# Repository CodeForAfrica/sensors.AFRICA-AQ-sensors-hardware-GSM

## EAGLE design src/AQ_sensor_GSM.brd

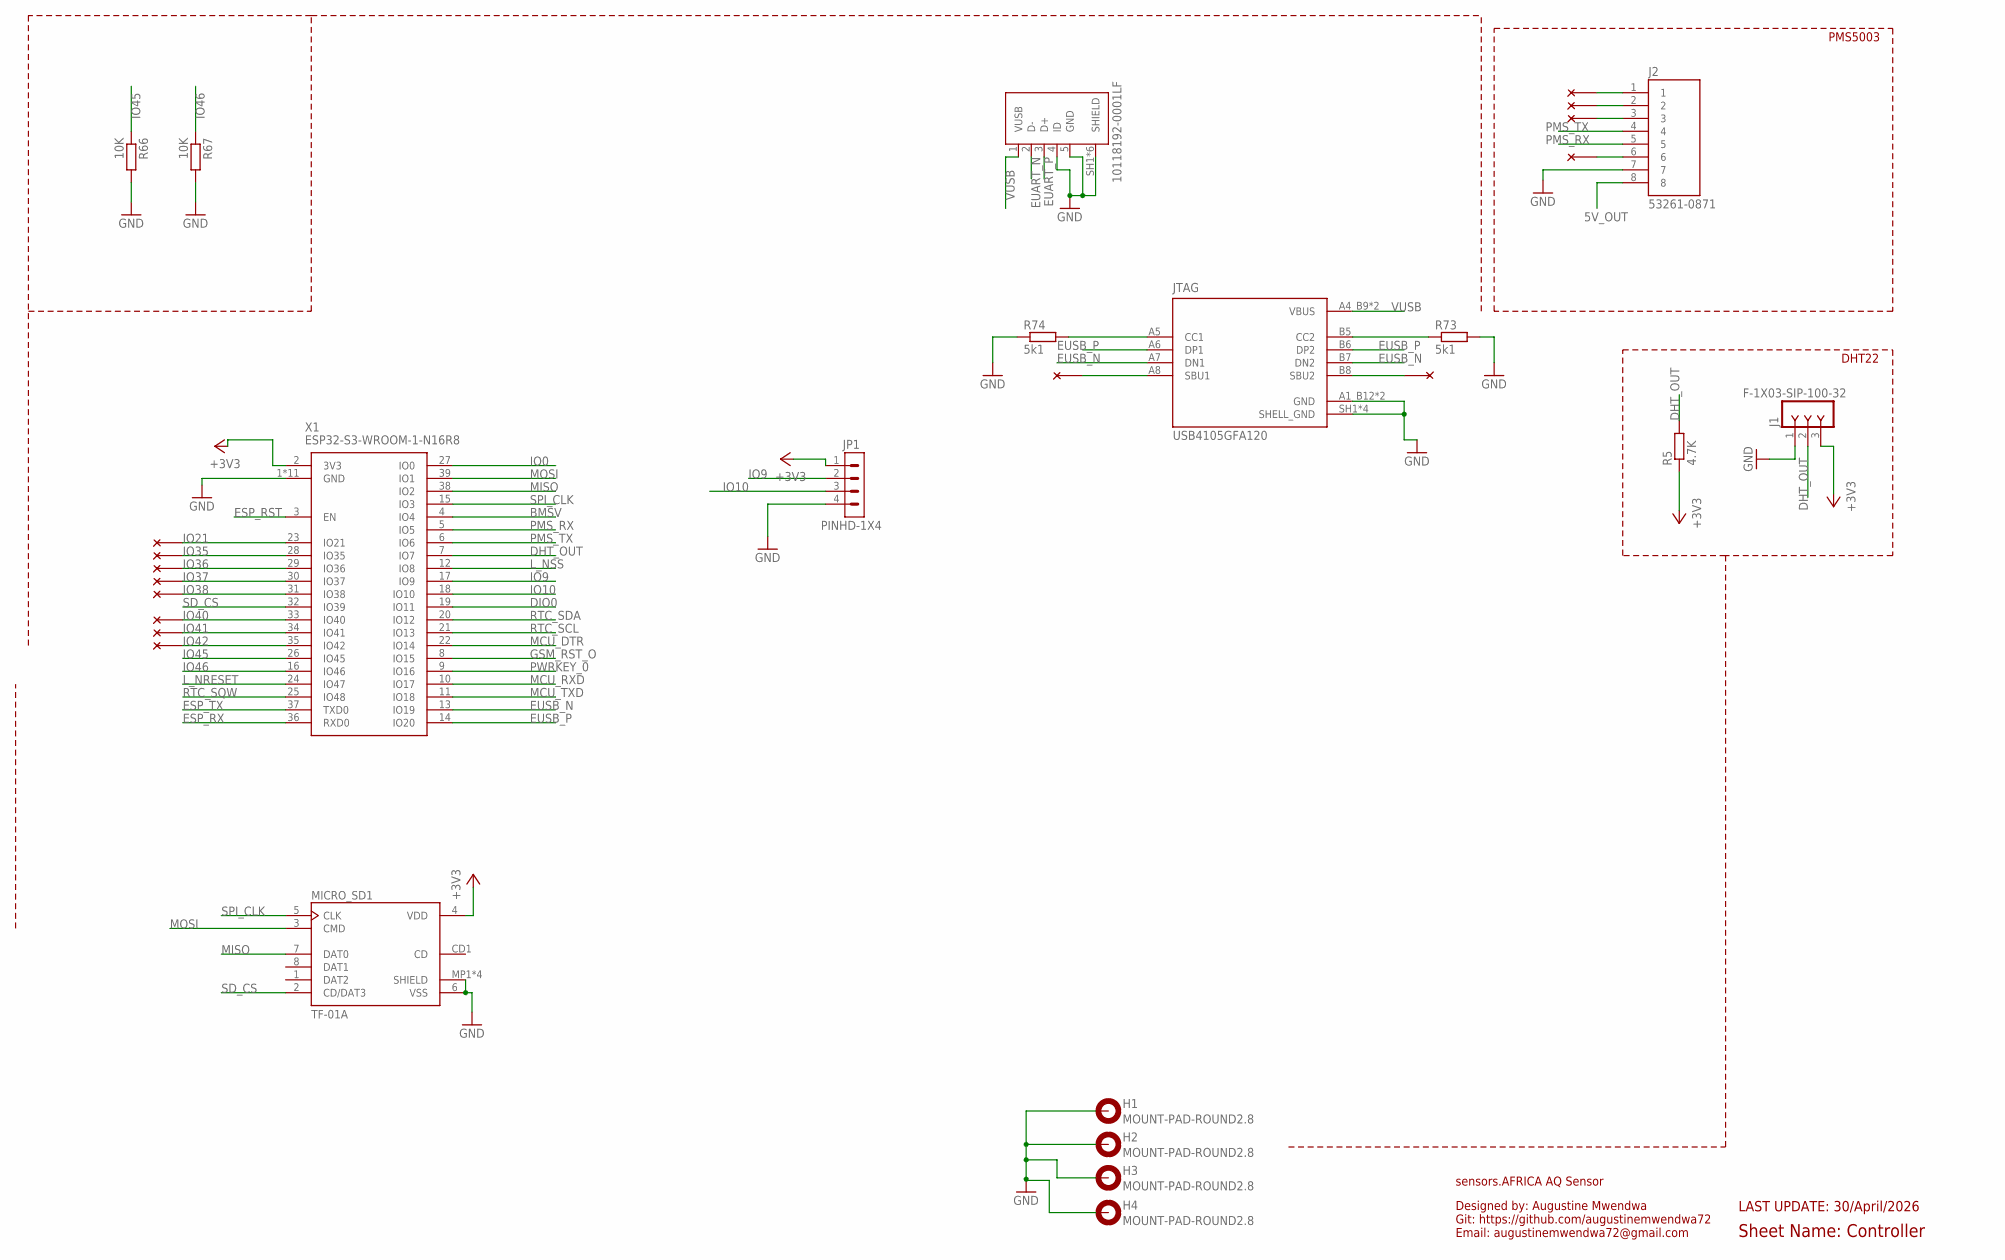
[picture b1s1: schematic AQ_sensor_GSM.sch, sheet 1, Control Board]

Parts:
ESP_UART: 10118192-0001LF; AMPHENOL_10118192-0001LF
H1, H2, H3, H4: MOUNT-PAD-ROUND2.8; 2,8-PAD
J1: F-1X03-SIP-100-32; SIP-100-03-32
J2: 53261-0871; MOLEX_53261-0871
JP1: PINHD-1X4; 1X04
JTAG: USB4105GFA120; GCT_USB4105GFA120
MICRO_SD1: TF-01A
R5: 4.7K; R0603
R66, R67: 10K; R0603
R73, R74: 5k1; R0603
X1: ESP32-S3-WROOM-1-N16R8; ESP32S3WROOM1N8R2

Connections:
5V_OUT: J2.8; also elsewhere on the board
+3V3: J1.3, JP1.1, MICRO_SD1.4 (VDD), R5.1, X1.2 (3V3); also elsewhere on the board
BMSV: X1.4 (IO4); also elsewhere on the board
DHT_OUT: J1.2, R5.2, X1.7 (IO7)
DIO0: X1.19 (IO11); also elsewhere on the board
ESP_RST: X1.3 (EN); also elsewhere on the board
ESP_RX: X1.36 (RXD0); also elsewhere on the board
ESP_TX: X1.37 (TXD0); also elsewhere on the board
EUART_N: ESP_UART.2 (D-); also elsewhere on the board
EUART_P: ESP_UART.3 (D+); also elsewhere on the board
EUSB_N: JTAG.A7 (DN1), JTAG.B7 (DN2), X1.13 (IO19); also elsewhere on the board
EUSB_P: JTAG.A6 (DP1), JTAG.B6 (DP2), X1.14 (IO20); also elsewhere on the board
GND: ESP_UART.4 (ID), ESP_UART.5 (GND), ESP_UART.SH1 (SHIELD), ESP_UART.SH2 (SHIELD), ESP_UART.SH3 (SHIELD), ESP_UART.SH4 (SHIELD), ESP_UART.SH5 (SHIELD), ESP_UART.SH6 (SHIELD), H1.B2,8, H2.B2,8, H3.B2,8, H4.B2,8, J1.1, J2.7, JP1.4, JTAG.A1_B12 (GND), JTAG.B1_A12 (GND), JTAG.SH1 (SHELL_GND), JTAG.SH2 (SHELL_GND), JTAG.SH3 (SHELL_GND), JTAG.SH4 (SHELL_GND), MICRO_SD1.6 (VSS), MICRO_SD1.MP1 (SHIELD), MICRO_SD1.MP2 (SHIELD), MICRO_SD1.MP3 (SHIELD), MICRO_SD1.MP4 (SHIELD), R66.2, R67.2, R73.2, R74.1, X1.1 (GND), X1.40 (GND), X1.41 (GND), X1.42 (GND), X1.43 (GND), X1.44 (GND), X1.45 (GND), X1.46 (GND), X1.47 (GND), X1.48 (GND), X1.49 (GND); also elsewhere on the board
GSM_RST_O: X1.8 (IO15); also elsewhere on the board
IO0: X1.27 (IO0); also elsewhere on the board
IO9: JP1.2, X1.17 (IO9)
IO10: JP1.3, X1.18 (IO10)
IO21: X1.23 (IO21)
IO35: X1.28 (IO35)
IO36: X1.29 (IO36)
IO37: X1.30 (IO37)
IO38: X1.31 (IO38)
IO40: X1.33 (IO40)
IO41: X1.34 (IO41)
IO42: X1.35 (IO42)
IO45: R66.1, X1.26 (IO45)
IO46: R67.1, X1.16 (IO46)
L_NRESET: X1.24 (IO47); also elsewhere on the board
L_NSS: X1.12 (IO8); also elsewhere on the board
MCU_DTR: X1.22 (IO14); also elsewhere on the board
MCU_RXD: X1.10 (IO17); also elsewhere on the board
MCU_TXD: X1.11 (IO18); also elsewhere on the board
MISO: MICRO_SD1.7 (DAT0), X1.38 (IO2); also elsewhere on the board
MOSI: MICRO_SD1.3 (CMD), X1.39 (IO1); also elsewhere on the board
unnamed: JTAG.A5 (CC1), R74.2
unnamed: JTAG.B5 (CC2), R73.1
PMS_RX: J2.5, X1.5 (IO5)
PMS_TX: J2.4, X1.6 (IO6)
PWRKEY_0: X1.9 (IO16); also elsewhere on the board
RTC_SCL: X1.21 (IO13); also elsewhere on the board
RTC_SDA: X1.20 (IO12); also elsewhere on the board
RTC_SQW: X1.25 (IO48); also elsewhere on the board
SD_CS: MICRO_SD1.2 (CD/DAT3), X1.32 (IO39)
SPI_CLK: MICRO_SD1.5 (CLK), X1.15 (IO3); also elsewhere on the board
VUSB: ESP_UART.1 (VUSB), JTAG.A4_B9 (VBUS), JTAG.B4_A9 (VBUS); also elsewhere on the board

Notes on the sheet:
sensors.AFRICA AQ Sensor
LAST UPDATE: 30/April/2026
PMS5003
DHT22
Designed by: Augustine Mwendwa Git: https://github.com/augustinemwendwa72 Email: augustinemwendwa72@gmail.com
Sheet Name: Controller

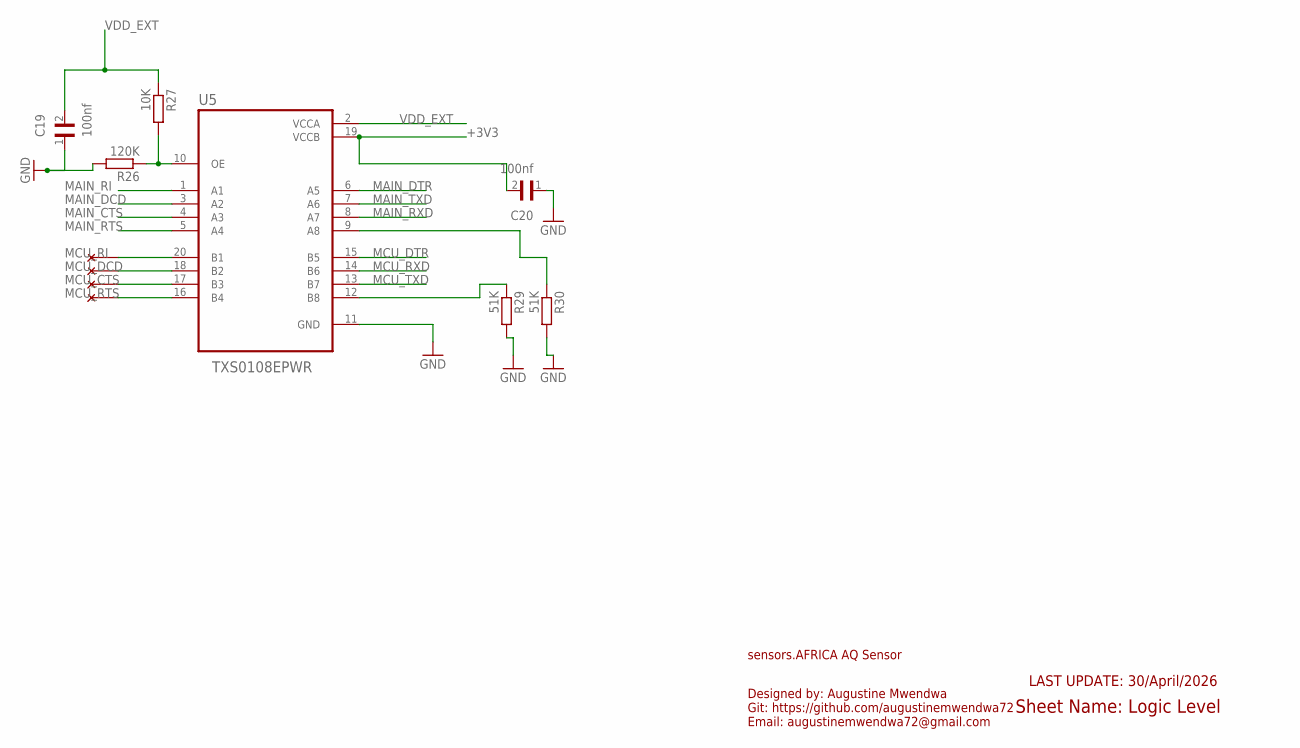
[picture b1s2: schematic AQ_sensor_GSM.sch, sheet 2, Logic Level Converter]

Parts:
C19, C20: 100nf; CAPC1608X90N
R26: 120K; R0603
R27: 10K; R0603
R29, R30: 51K; R0603
U5: TXS0108EPWR; SOP65P640X120-20N

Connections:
+3V3: C20.2, U5.19 (VCCB); also elsewhere on the board
GND: C19.1, C20.1, R26.2, R29.2, R30.2, U5.11 (GND); also elsewhere on the board
MAIN_CTS: U5.4 (A3); also elsewhere on the board
MAIN_DCD: U5.3 (A2); also elsewhere on the board
MAIN_DTR: U5.6 (A5); also elsewhere on the board
MAIN_RI: U5.1 (A1); also elsewhere on the board
MAIN_RTS: U5.5 (A4); also elsewhere on the board
MAIN_RXD: U5.8 (A7); also elsewhere on the board
MAIN_TXD: U5.7 (A6); also elsewhere on the board
MCU_CTS: U5.17 (B3)
MCU_DCD: U5.18 (B2)
MCU_DTR: U5.15 (B5); also elsewhere on the board
MCU_RI: U5.20 (B1)
MCU_RTS: U5.16 (B4)
MCU_RXD: U5.14 (B6); also elsewhere on the board
MCU_TXD: U5.13 (B7); also elsewhere on the board
unnamed: R26.1, R27.2, U5.10 (OE)
unnamed: R30.1, U5.9 (A8)
unnamed: R29.1, U5.12 (B8)
VDD_EXT: C19.2, R27.1, U5.2 (VCCA); also elsewhere on the board

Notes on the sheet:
sensors.AFRICA AQ Sensor
Sheet Name: Logic Level
Designed by: Augustine Mwendwa Git: https://github.com/augustinemwendwa72 Email: augustinemwendwa72@gmail.com
LAST UPDATE: 30/April/2026

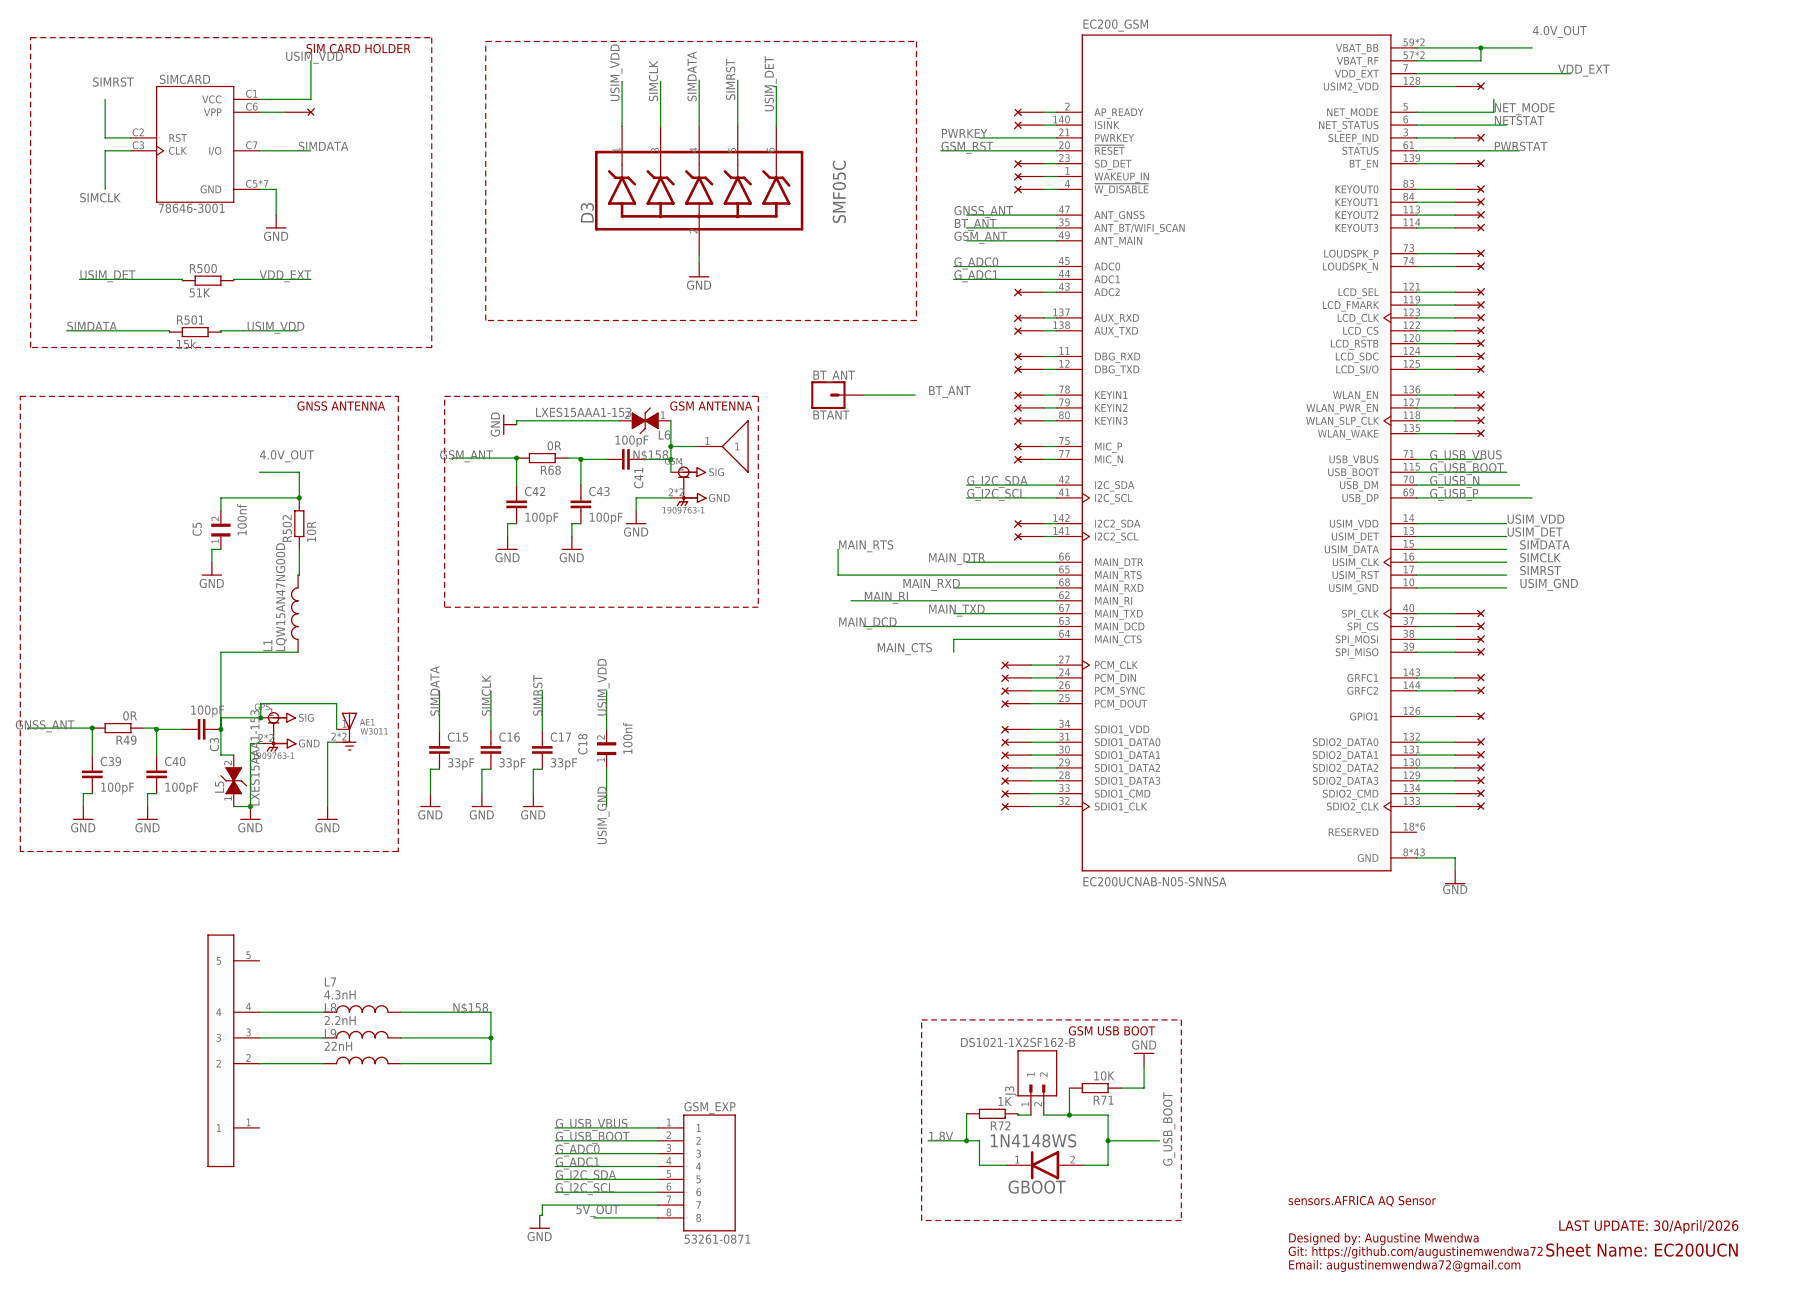
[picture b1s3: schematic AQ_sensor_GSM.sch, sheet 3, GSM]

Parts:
AE1: W3011; XDCR_W3011
BT_ANT: BTANT; 1X01
C3, C39, C40, C41, C42, C43: 100pF; 0603
C5, C18: 100nf; CAPC1608X90N
C15, C16, C17: 33pF; C0603
D3: SEMTECH_SMF05CSEMTECH_SMF05C_0_0; SEMTECH_SMF05C_0
EC200_GSM: EC200UCNAB-N05-SNNSA; XCVR_EC200UCNAB-N05-SNNSA
GBOOT: ON_SEMI_1N4148WSON_SEMI_1N4148WS_0_0; ON_SEMI_1N4148WS_0
GPS: 1909763-1; TE_1909763-1
GSM: 1909763-1; TE_1909763-1
GSM_EXP: 53261-0871; MOLEX_53261-0871
J3: DS1021-1X2SF162-B; CONNFLY_DS1021-1X2SF162-B
L1: LQW15AN47NG00D; INDC1005X60N
L5, L6: LXES15AAA1-153; INDC1005X45
L7: 4.3nH; INDC1005X60N
L8: 2.2nH; INDC1005X60N
L9: 22nH; INDC1005X60N
R49, R68: 0R; R0603
R71: 10K; R0603
R72: 1K; R0603
R500: 51K; R0603
R501: 15k; R0603
R502: 10R; R0603
SIMCARD: 78646-3001; MOLEX_78646-3001
U$107: GSM_SPRING_ANTENNA
U$109: ADCH002_V1

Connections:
1.8V: GBOOT.1 (CATHODE), R72.2; also elsewhere on the board
4.0V_OUT: C5.2, EC200_GSM.57 (VBAT_RF), EC200_GSM.58 (VBAT_RF), EC200_GSM.59 (VBAT_BB), EC200_GSM.60 (VBAT_BB), R502.2; also elsewhere on the board
5V_OUT: GSM_EXP.8; also elsewhere on the board
BT_ANT: BT_ANT.1, EC200_GSM.35 (ANT_BT/WIFI_SCAN)
GND: AE1.2 (GND), AE1.3 (GND), C5.1, C15.2, C16.2, C17.2, C39.2, C40.2, C42.2, C43.2, D3.2 (ANODE), EC200_GSM.8 (GND), EC200_GSM.9 (GND), EC200_GSM.19 (GND), EC200_GSM.22 (GND), EC200_GSM.36 (GND), EC200_GSM.46 (GND), EC200_GSM.48 (GND), EC200_GSM.50 (GND), EC200_GSM.51 (GND), EC200_GSM.52 (GND), EC200_GSM.53 (GND), EC200_GSM.54 (GND), EC200_GSM.56 (GND), EC200_GSM.72 (GND), EC200_GSM.76 (GND), EC200_GSM.85 (GND), EC200_GSM.86 (GND), EC200_GSM.87 (GND), EC200_GSM.88 (GND), EC200_GSM.89 (GND), EC200_GSM.90 (GND), EC200_GSM.91 (GND), EC200_GSM.92 (GND), EC200_GSM.93 (GND), EC200_GSM.94 (GND), EC200_GSM.95 (GND), EC200_GSM.96 (GND), EC200_GSM.97 (GND), EC200_GSM.98 (GND), EC200_GSM.99 (GND), EC200_GSM.100 (GND), EC200_GSM.101 (GND), EC200_GSM.102 (GND), EC200_GSM.103 (GND), EC200_GSM.104 (GND), EC200_GSM.105 (GND), EC200_GSM.106 (GND), EC200_GSM.107 (GND), EC200_GSM.108 (GND), EC200_GSM.109 (GND), EC200_GSM.110 (GND), EC200_GSM.111 (GND), EC200_GSM.112 (GND), GPS.2 (GND), GPS.3 (GND), GSM.2 (GND), GSM.3 (GND), GSM_EXP.7, L5.1, L6.2, R71.1, SIMCARD.C5 (GND), SIMCARD.G1 (GND), SIMCARD.G2 (GND), SIMCARD.G3 (GND), SIMCARD.G4 (GND), SIMCARD.G5 (GND), SIMCARD.G6 (GND); also elsewhere on the board
GNSS_ANT: C39.1, EC200_GSM.47 (ANT_GNSS), R49.2
GSM_ANT: C42.1, EC200_GSM.49 (ANT_MAIN), R68.2
GSM_RST: EC200_GSM.20 (!RESET); also elsewhere on the board
G_ADC0: EC200_GSM.45 (ADC0), GSM_EXP.3
G_ADC1: EC200_GSM.44 (ADC1), GSM_EXP.4
G_I2C_SCL: EC200_GSM.41 (I2C_SCL), GSM_EXP.6
G_I2C_SDA: EC200_GSM.42 (I2C_SDA), GSM_EXP.5
G_USB_BOOT: EC200_GSM.115 (USB_BOOT), GBOOT.2 (ANODE), GSM_EXP.2, J3.2, R71.2
G_USB_N: EC200_GSM.70 (USB_DM); also elsewhere on the board
G_USB_P: EC200_GSM.69 (USB_DP); also elsewhere on the board
G_USB_VBUS: EC200_GSM.71 (USB_VBUS), GSM_EXP.1
MAIN_CTS: EC200_GSM.64 (MAIN_CTS); also elsewhere on the board
MAIN_DCD: EC200_GSM.63 (MAIN_DCD); also elsewhere on the board
MAIN_DTR: EC200_GSM.66 (MAIN_DTR); also elsewhere on the board
MAIN_RI: EC200_GSM.62 (MAIN_RI); also elsewhere on the board
MAIN_RTS: EC200_GSM.65 (MAIN_RTS); also elsewhere on the board
MAIN_RXD: EC200_GSM.68 (MAIN_RXD); also elsewhere on the board
MAIN_TXD: EC200_GSM.67 (MAIN_TXD); also elsewhere on the board
unnamed: L1.2, R502.1
unnamed: AE1.1 (FEED), C3.1, GPS.1 (SIG), L1.1, L5.2
unnamed: C3.2, C40.1, R49.1
unnamed: C41.2, C43.1, R68.1
unnamed: C41.1, GSM.1 (SIG), L6.1, L7.2, L8.2, L9.2, U$107.1
unnamed: L8.1, U$109.3
unnamed: L9.1, U$109.2
unnamed: L7.1, U$109.4
unnamed: J3.1, R72.1
NETSTAT: EC200_GSM.6 (NET_STATUS); also elsewhere on the board
NET_MODE: EC200_GSM.5 (NET_MODE); also elsewhere on the board
PWRKEY: EC200_GSM.21 (PWRKEY); also elsewhere on the board
PWRSTAT: EC200_GSM.61 (STATUS); also elsewhere on the board
SIMCLK: C16.1, D3.3 (2_CATHODE), EC200_GSM.16 (USIM_CLK), SIMCARD.C3 (CLK)
SIMDATA: C15.1, D3.4 (3_CATHODE), EC200_GSM.15 (USIM_DATA), R501.1, SIMCARD.C7 (I/O)
SIMRST: C17.1, D3.5 (4_CATHODE), EC200_GSM.17 (USIM_RST), SIMCARD.C2 (RST)
USIM_DET: D3.6 (5_CATHODE), EC200_GSM.13 (USIM_DET), R500.1
USIM_GND: C18.1, EC200_GSM.10 (USIM_GND)
USIM_VDD: C18.2, D3.1 (1_CATHODE), EC200_GSM.14 (USIM_VDD), R501.2, SIMCARD.C1 (VCC)
VDD_EXT: EC200_GSM.7 (VDD_EXT), R500.2; also elsewhere on the board

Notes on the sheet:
SIM CARD HOLDER
GSM ANTENNA
GNSS ANTENNA
GSM USB BOOT
sensors.AFRICA AQ Sensor
Sheet Name: EC200UCN
Designed by: Augustine Mwendwa Git: https://github.com/augustinemwendwa72 Email: augustinemwendwa72@gmail.com
LAST UPDATE: 30/April/2026

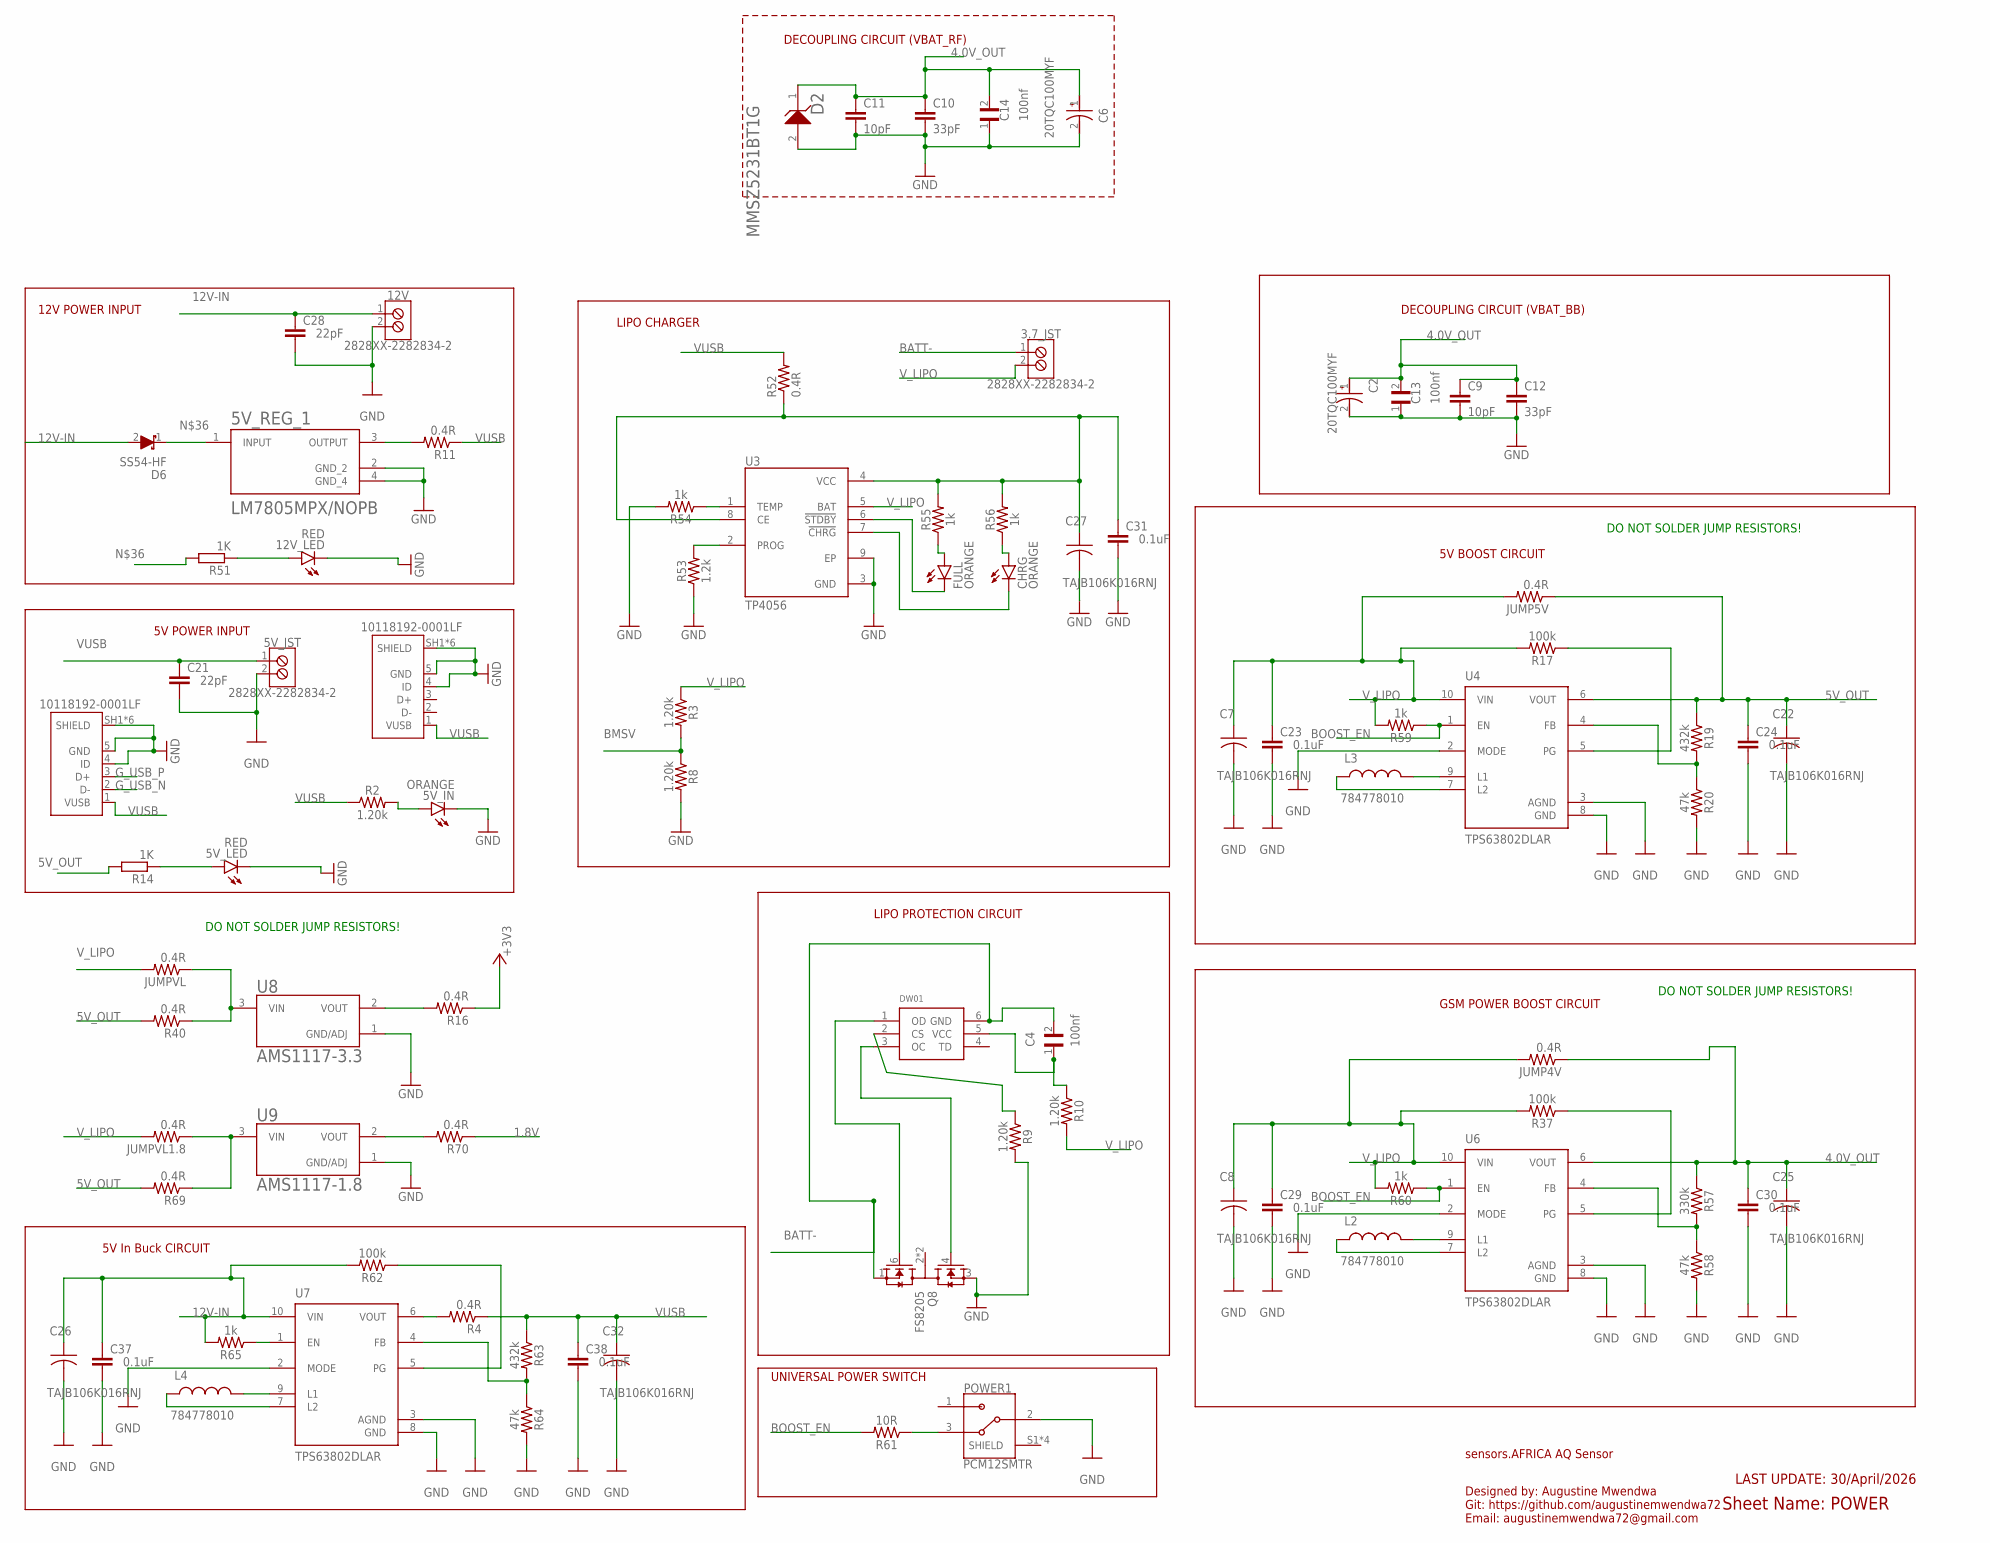
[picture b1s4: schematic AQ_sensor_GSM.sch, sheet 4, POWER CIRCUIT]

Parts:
3.7_JST, 5V_JST, 12V: 2828XX-2282834-2; TERMBLK_254-2N
5V_IN: ORANGE; CHIP-LED0603
5V_LED, 12V_LED: RED; CHIP-LED0603
5V_REG_1: LM7805MPX/NOPB; VREG_LM7805MPX/NOPB
C2, C6: 20TQC100MYF; CAP_20TQC100MYF
C4, C13, C14: 100nf; CAPC1608X90N
C7, C8, C22, C25, C26, C27, C32: TAJB106K016RNJ; CAP_TANT_B
C9, C11: 10pF; C0603
C10, C12: 33pF; C0603
C21, C28: 22pF; C0603
C23, C24, C29, C30, C31, C37, C38: 0.1uF; C0603
CHRG: ORANGE; CHIP-LED0603
D2: ON_SEMICONDUCTOR_MMSZ5231BT1GON_SEMICONDUCTOR_MMS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; ON_SEMICONDUCTOR_MMSZ5231BT1G_0
D6: SS54-HF; DIOM5025X220N
DW01: DW01-P; SOT23-6L
FULL: ORANGE; CHIP-LED0603
JUMP4V, JUMP5V: 0.4R; RES_0805
JUMPVL, JUMPVL1.8: 0.4R; RES_0805
L2, L3, L4: 784778010
POWER: 10118192-0001LF; AMPHENOL_10118192-0001LF
POWER1: PCM12SMTR; SW_PCM12SMTR
Q8: FS8205; SOT95P280X145-6N
QUEC_C: 10118192-0001LF; AMPHENOL_10118192-0001LF
R2, R3, R8, R9, R10: 1.20k; 0603
R4, R11, R16, R40, R52, R69, R70: 0.4R; RES_0805
R14, R51: 1K; R0603
R17, R37, R62: 100k; 0603
R19, R63: 432k; 0603
R20, R58, R64: 47k; 0603
R53: 1.2k; 0603
R54, R55, R56, R59, R60, R65: 1k; 0603
R57: 330k; 0603
R61: 10R; 0603
U3: TP4056; SOP127P600X175-9N
U4, U6, U7: TPS63802DLAR; VREG_TPS63802DLAR
U8: AMS1117-3.3; SOT229P700X180-4N
U9: AMS1117-1.8; SOT229P700X180-4N

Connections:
1.8V: R70.1; also elsewhere on the board
4.0V_OUT: C2.1, C6.1, C9.1, C10.1, C11.1, C12.1, C13.2, C14.2, C25.1, C30.1, D2.1 (K), JUMP4V.1, R57.1, U6.6 (VOUT); also elsewhere on the board
5V_OUT: C22.1, C24.1, JUMP5V.1, R14.2, R19.1, R40.2, R69.2, U4.6 (VOUT); also elsewhere on the board
12V-IN: 12V.1, C26.1, C28.1, C37.1, D6.2 (A), R62.2, R65.2, U7.10 (VIN)
+3V3: R16.1; also elsewhere on the board
BATT-: 3.7_JST.1, C4.2, DW01.6 (GND), Q8.1 (S1)
BMSV: R3.2, R8.1; also elsewhere on the board
BOOST_EN: R59.1, R60.1, R61.2, U4.1 (EN), U6.1 (EN)
GND: 5V_IN.C, 5V_JST.2, 5V_LED.C, 5V_REG_1.2 (GND_2), 5V_REG_1.4 (GND_4), 12V.2, 12V_LED.C, C2.2, C6.2, C7.2, C8.2, C9.2, C10.2, C11.2, C12.2, C13.1, C14.1, C21.2, C22.2, C23.2, C24.2, C25.2, C26.2, C27.2, C28.2, C29.2, C30.2, C31.2, C32.2, C37.2, C38.2, D2.2 (A), POWER.4 (ID), POWER.5 (GND), POWER.SH1 (SHIELD), POWER.SH2 (SHIELD), POWER.SH3 (SHIELD), POWER.SH4 (SHIELD), POWER.SH5 (SHIELD), POWER.SH6 (SHIELD), POWER1.2, Q8.3 (S2), QUEC_C.4 (ID), QUEC_C.5 (GND), QUEC_C.SH1 (SHIELD), QUEC_C.SH2 (SHIELD), QUEC_C.SH3 (SHIELD), QUEC_C.SH4 (SHIELD), QUEC_C.SH5 (SHIELD), QUEC_C.SH6 (SHIELD), R8.2, R9.2, R20.2, R53.1, R54.2, R58.2, R64.2, U3.3 (GND), U3.9 (EP), U4.2 (MODE), U4.3 (AGND), U4.8 (GND), U6.2 (MODE), U6.3 (AGND), U6.8 (GND), U7.2 (MODE), U7.3 (AGND), U7.8 (GND), U8.1 (GND/ADJ), U9.1 (GND/ADJ); also elsewhere on the board
G_USB_N: QUEC_C.2 (D-); also elsewhere on the board
G_USB_P: QUEC_C.3 (D+); also elsewhere on the board
unnamed: DW01.1 (OD), Q8.6 (G1)
unnamed: 5V_IN.A, R2.2
unnamed: L3.2, U4.9 (L1)
unnamed: L3.1, U4.7 (L2)
unnamed: L2.2, U6.9 (L1)
unnamed: R17.1, U4.5 (PG)
unnamed: DW01.3 (OC), Q8.4 (G2)
unnamed: POWER1.3, R61.1
unnamed: R19.2, R20.1, U4.4 (FB)
unnamed: L2.1, U6.7 (L2)
unnamed: 5V_LED.A, R14.1
unnamed: 5V_REG_1.1 (INPUT), D6.1 (K), R51.2
unnamed: C4.1, DW01.5 (VCC), R10.1
unnamed: R37.1, U6.5 (PG)
unnamed: R57.2, R58.1, U6.4 (FB)
unnamed: DW01.2 (CS), R9.1
unnamed: 12V_LED.A, R51.1
unnamed: R4.2, U7.6 (VOUT)
unnamed: 5V_REG_1.3 (OUTPUT), R11.2
unnamed: JUMPVL.1, R40.1, U8.3 (VIN)
unnamed: R16.2, U8.2 (VOUT)
unnamed: C27.1, C31.1, R52.1, R55.2, R56.2, U3.4 (VCC), U3.8 (CE)
unnamed: R53.2, U3.2 (PROG)
unnamed: FULL.A, R55.1
unnamed: CHRG.A, R56.1
unnamed: FULL.C, U3.6 (!STDBY)
unnamed: CHRG.C, U3.7 (!CHRG)
unnamed: R54.1, U3.1 (TEMP)
unnamed: L4.2, U7.9 (L1)
unnamed: L4.1, U7.7 (L2)
unnamed: R62.1, U7.5 (PG)
unnamed: R63.2, R64.1, U7.4 (FB)
unnamed: R65.1, U7.1 (EN)
unnamed: JUMPVL1.8.1, R69.1, U9.3 (VIN)
unnamed: R70.2, U9.2 (VOUT)
VUSB: 5V_JST.1, C21.1, C32.1, C38.1, POWER.1 (VUSB), QUEC_C.1 (VUSB), R2.1, R4.1, R11.1, R52.2, R63.1; also elsewhere on the board
V_LIPO: 3.7_JST.2, C7.1, C8.1, C23.1, C29.1, JUMP4V.2, JUMP5V.2, JUMPVL.2, JUMPVL1.8.2, R3.1, R10.2, R17.2, R37.2, R59.2, R60.2, U3.5 (BAT), U4.10 (VIN), U6.10 (VIN)

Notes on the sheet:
DECOUPLING CIRCUIT (VBAT_RF)
DECOUPLING CIRCUIT (VBAT_BB)
GSM POWER BOOST CIRCUIT
5V BOOST CIRCUIT
LIPO PROTECTION CIRCUIT
LIPO CHARGER
12V POWER INPUT
5V POWER INPUT
UNIVERSAL POWER SWITCH
5V In Buck CIRCUIT
DO NOT SOLDER JUMP RESISTORS!
sensors.AFRICA AQ Sensor
Sheet Name: POWER
Designed by: Augustine Mwendwa Git: https://github.com/augustinemwendwa72 Email: augustinemwendwa72@gmail.com
LAST UPDATE: 30/April/2026

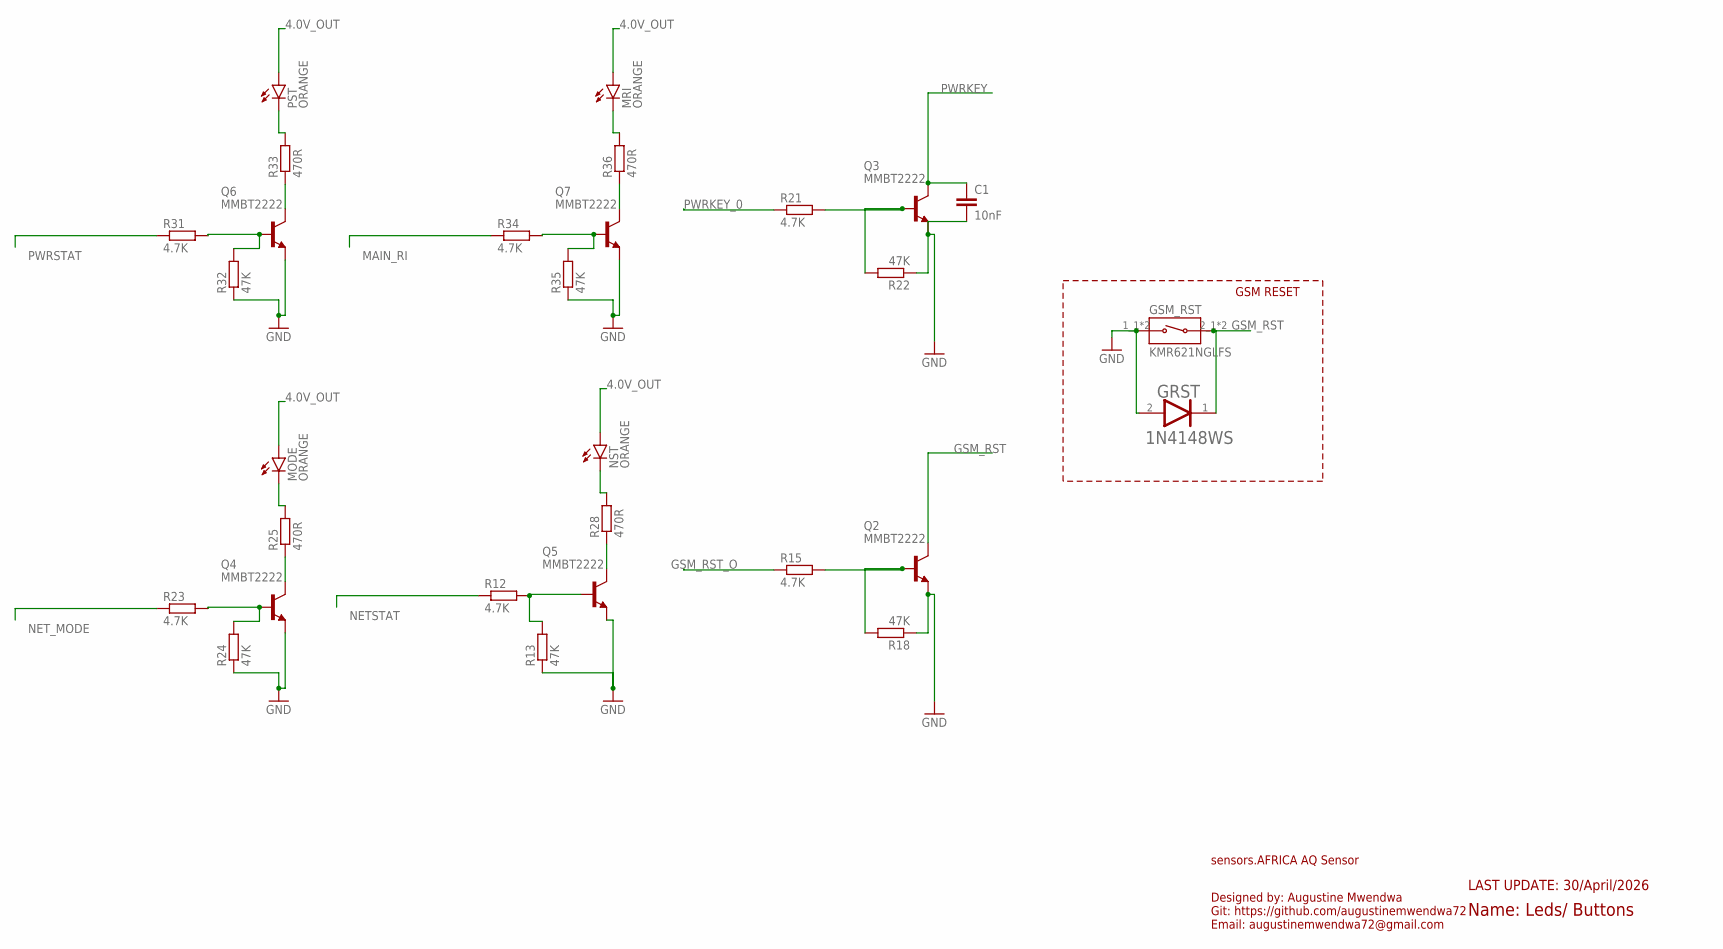
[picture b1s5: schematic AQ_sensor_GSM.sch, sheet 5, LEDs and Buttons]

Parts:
C1: 10nF; 0603
GRST: ON_SEMI_1N4148WSON_SEMI_1N4148WS_0_0; ON_SEMI_1N4148WS_0
GSM_RST: KMR621NGLFS; SW_KMR621NGLFS
MODE: ORANGE; CHIP-LED0603
MRI: ORANGE; CHIP-LED0603
NST: ORANGE; CHIP-LED0603
PST: ORANGE; CHIP-LED0603
Q2, Q3, Q4, Q5, Q6, Q7: MMBT2222; SOT23-BEC
R12, R15, R21, R23, R31, R34: 4.7K; R0603
R13, R18, R22, R24, R32, R35: 47K; R0603
R25, R28, R33, R36: 470R; R0603

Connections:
4.0V_OUT: MODE.A, MRI.A, NST.A, PST.A; also elsewhere on the board
GND: C1.2, GRST.2 (ANODE), GSM_RST.1_1 (1), GSM_RST.1_2 (1), Q2.E, Q3.E, Q4.E, Q5.E, Q6.E, Q7.E, R13.1, R18.1, R22.1, R24.1, R32.1, R35.1; also elsewhere on the board
GSM_RST: GRST.1 (CATHODE), GSM_RST.2_1 (2), GSM_RST.2_2 (2), Q2.C; also elsewhere on the board
GSM_RST_O: R15.1; also elsewhere on the board
MAIN_RI: R34.1; also elsewhere on the board
unnamed: Q2.B, R15.2, R18.2
unnamed: Q3.B, R21.2, R22.2
unnamed: Q5.B, R12.2, R13.2
unnamed: Q4.B, R23.2, R24.2
unnamed: Q6.B, R31.2, R32.2
unnamed: Q4.C, R25.1
unnamed: MODE.C, R25.2
unnamed: Q6.C, R33.1
unnamed: Q5.C, R28.1
unnamed: NST.C, R28.2
unnamed: PST.C, R33.2
unnamed: Q7.B, R34.2, R35.2
unnamed: Q7.C, R36.1
unnamed: MRI.C, R36.2
NETSTAT: R12.1; also elsewhere on the board
NET_MODE: R23.1; also elsewhere on the board
PWRKEY: C1.1, Q3.C; also elsewhere on the board
PWRKEY_0: R21.1; also elsewhere on the board
PWRSTAT: R31.1; also elsewhere on the board

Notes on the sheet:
GSM RESET
sensors.AFRICA AQ Sensor
Name: Leds/ Buttons
Designed by: Augustine Mwendwa Git: https://github.com/augustinemwendwa72 Email: augustinemwendwa72@gmail.com
LAST UPDATE: 30/April/2026

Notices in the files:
parts and their libraries:
SparkFun-PowerSymbols: Licensing: Creative Commons ShareAlike 4.0 International - https://creativecommons.org/licenses/by-sa/4.0
